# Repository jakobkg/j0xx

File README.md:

# j0xx
A controller inspired by the Frame1 and Smashbox controllers

## Case
### BOM
 - 36 M2 screws, countersunk head recommended
   - 28x 10mm
   - 8x 5mm
 - 18 M2 threaded spacers
   - 18x 10mm
 - 35 pieces of wire, stranded or solid core

## PCBs
The PCB files in this repository are all made using KiCad 6, and may not work properly in earlier versions. Most files are only plain PCBs, but the "main board" files also hold part numbers and information needed to place an order including assembly through JLCPCB.

## Build notes
***Due to height constraints, surface mounted LEDs can not be used along with low profile Choc switches in this iteration of the design***

The controller case is designed to be made out of cut sheets of material, such as laser cut wood/acrylic or metal.
I recommend a thickness of 3mm for the top plate for use with low profile Choc switches, and 6mm for use with regular MX switches to ensure keycaps protrude nicely without the sides of the switches being exposed.
The switch mounting plate needs to be 1.5mm thick to fit the Cherry MX/Kailh Choc design specs and ensure a good fit, thinner plates may cause poor mounting and thicker plates will interfere with Choc switch mounting.

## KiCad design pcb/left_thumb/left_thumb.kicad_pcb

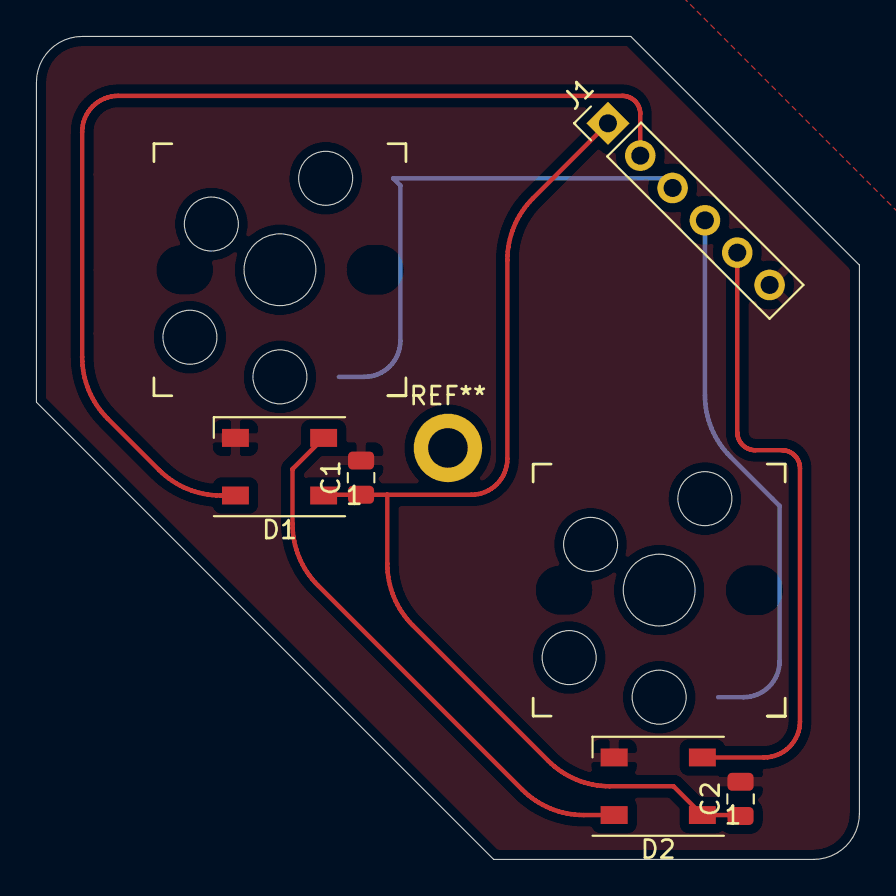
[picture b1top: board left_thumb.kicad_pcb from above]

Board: 2 copper layers, 45.7 x 45.7 mm, 7 parts (0 on the bottom side), 7 nets.

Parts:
C1, C2: C; C_0805_2012Metric
D1, D2: WS2812B; LED_WS2812B_PLCC4_5.0x5.0mm_P3.2mm
J1: Conn_01x06; PinHeader_1x06_P2.54mm_Vertical
SW1, SW2: SW_Push; MX+Choc_socket

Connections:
+5V: C1.1, C2.1, D1.1, D2.1, J1.1
BTN_MODX: J1.3, SW1.1
BTN_MODY: J1.4, SW2.1
GND: C1.2, C2.2, D1.3, D2.3, J1.6, SW1.2, SW2.2
LED_IN: D1.4, J1.2
LED_OUT: D2.2, J1.5
unnamed: D1.2, D2.4

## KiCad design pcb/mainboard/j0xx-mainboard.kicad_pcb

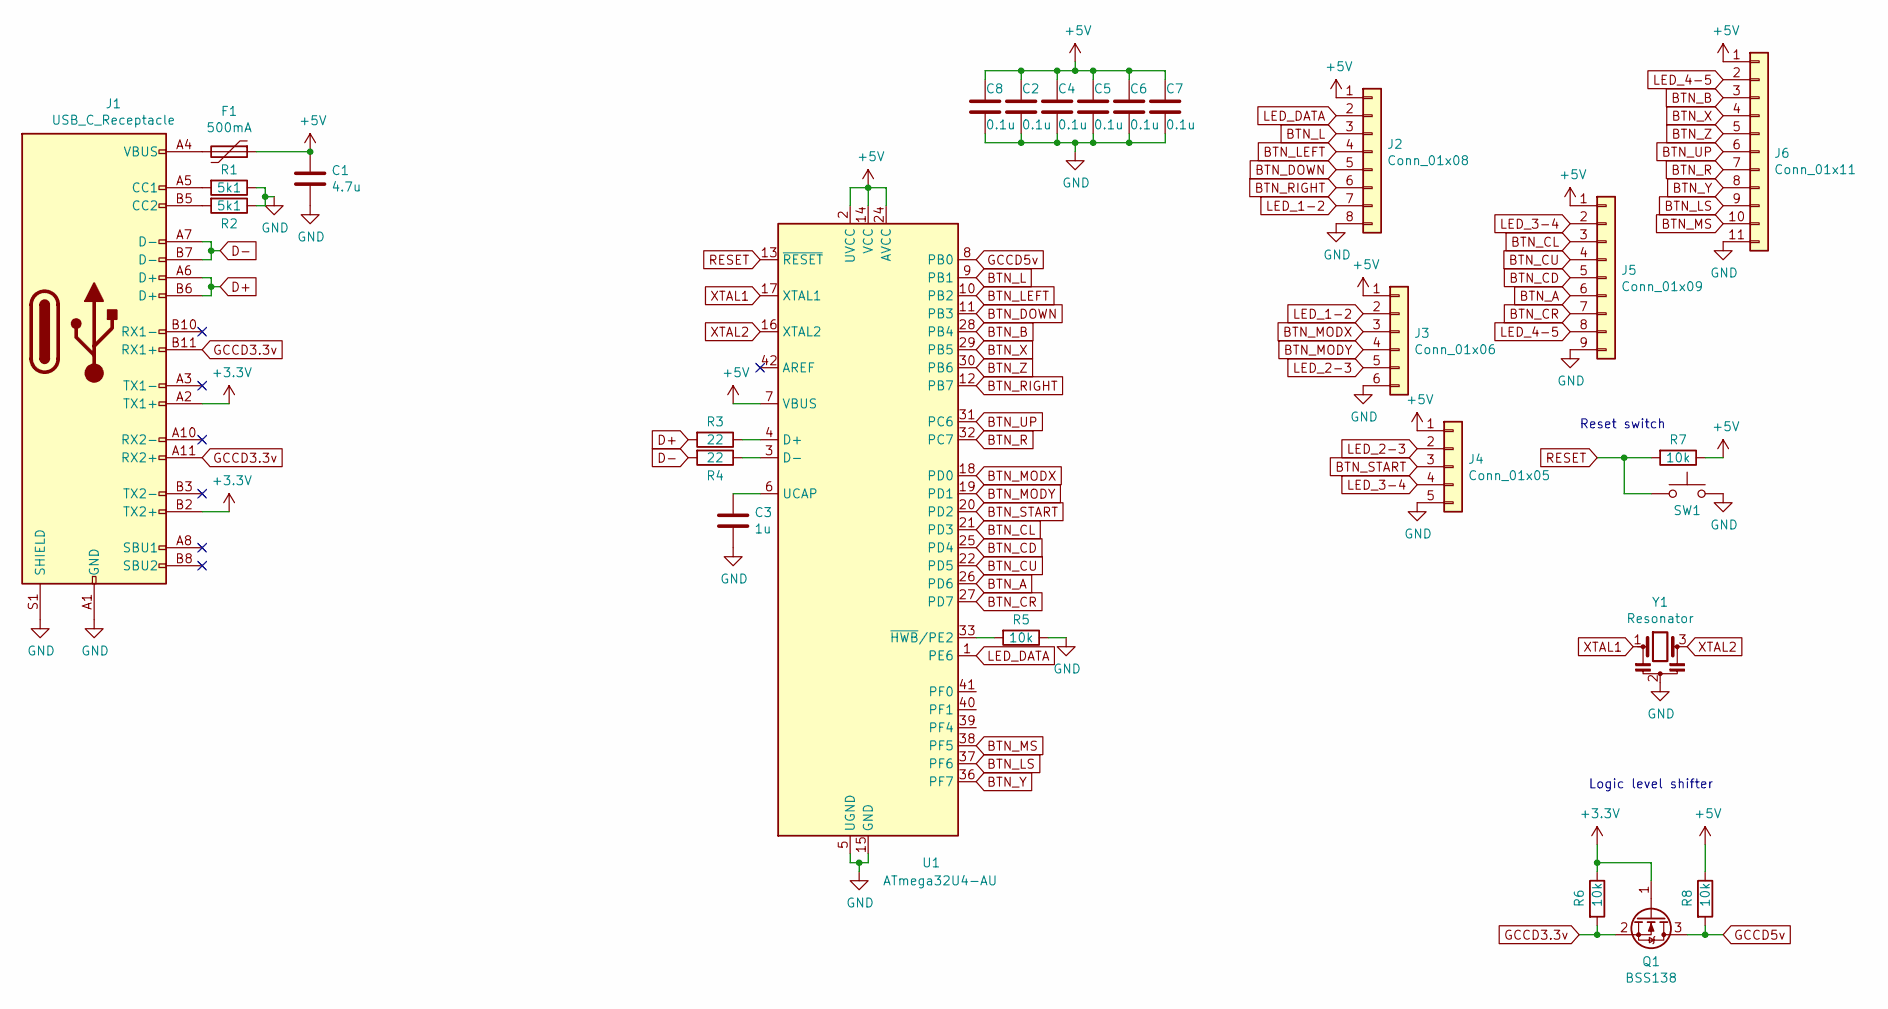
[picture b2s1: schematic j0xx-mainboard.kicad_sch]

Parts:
C1: 4.7u; C_0805_2012Metric; LCSC C1779
C2, C4, C5, C6, C7, C8: 0.1u; C_0805_2012Metric; LCSC C28233
C3: 1u; C_0805_2012Metric; LCSC C28323
F1: 500mA; Fuse_1206_3216Metric; LCSC C261952
J1: USB_C_Receptacle; USB_C_LCSC_C456013; LCSC C456013
J2: Conn_01x08; PinHeader_1x08_P2.54mm_Vertical
J3: Conn_01x06; PinHeader_1x06_P2.54mm_Vertical
J4: Conn_01x05; PinHeader_1x05_P2.54mm_Vertical
J5: Conn_01x09; PinHeader_1x09_P2.54mm_Vertical
J6: Conn_01x11; PinHeader_1x11_P2.54mm_Vertical
Q1: BSS138; SOT-23; LCSC C427380
R1, R2: 5k1; R_0805_2012Metric; LCSC C27834
R3, R4: 22; R_0805_2012Metric; LCSC C17561
R5, R6, R7, R8: 10k; R_0805_2012Metric; LCSC C17414
SW1: reset; TestPoint_2Pads_Pitch2.54mm_Drill0.8mm
U1: ATmega32U4-AU; TQFP-44_10x10mm_P0.8mm; LCSC C112161
Y1: Resonator; Resonator_SMD_Murata_CSTxExxV-3Pin_3.0x1.1mm; LCSC C341521

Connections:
+3V3: J1.A2 (TX1+), J1.B2 (TX2+), Q1.1 (G), R6.1
+5V: C1.1, C2.1, C4.1, C5.1, C6.1, C7.1, C8.1, F1.1, J2.1, J3.1, J4.1, J5.1, J6.1, R7.1, R8.1, U1.2 (UVCC), U1.7 (VBUS), U1.14 (VCC), U1.24 (AVCC), U1.34 (VCC), U1.44 (AVCC)
BTN_A: J5.6, U1.26 (PD6)
BTN_B: J6.3, U1.28 (PB4)
BTN_CD: J5.5, U1.25 (PD4)
BTN_CL: J5.3, U1.21 (PD3)
BTN_CR: J5.7, U1.27 (PD7)
BTN_CU: J5.4, U1.22 (PD5)
BTN_DOWN: J2.5, U1.11 (PB3)
BTN_L: J2.3, U1.9 (PB1)
BTN_LEFT: J2.4, U1.10 (PB2)
BTN_LS: J6.9, U1.37 (PF6)
BTN_MODX: J3.3, U1.18 (PD0)
BTN_MODY: J3.4, U1.19 (PD1)
BTN_MS: J6.10, U1.38 (PF5)
BTN_R: J6.7, U1.32 (PC7)
BTN_RIGHT: J2.6, U1.12 (PB7)
BTN_START: J4.3, U1.20 (PD2)
BTN_UP: J6.6, U1.31 (PC6)
BTN_X: J6.4, U1.29 (PB5)
BTN_Y: J6.8, U1.36 (PF7)
BTN_Z: J6.5, U1.30 (PB6)
D+: J1.A6 (D+), J1.B6 (D+), R3.2
D-: J1.A7 (D-), J1.B7 (D-), R4.2
GCCD3.3v: J1.A11 (RX2+), J1.B11 (RX1+), Q1.2 (S), R6.2
GCCD5v: Q1.3 (D), R8.2, U1.8 (PB0)
GND: C1.2, C2.2, C3.2, C4.2, C5.2, C6.2, C7.2, C8.2, J1.A1 (GND), J1.A12 (GND), J1.B1 (GND), J1.B12 (GND), J1.S1 (SHIELD), J2.8, J3.6, J4.5, J5.9, J6.11, R1.1, R2.1, R5.1, SW1.2, U1.5 (UGND), U1.15 (GND), U1.23 (GND), U1.35 (GND), U1.43 (GND), Y1.2
LED_1-2: J2.7, J3.2
LED_2-3: J3.5, J4.2
LED_3-4: J4.4, J5.2
LED_4-5: J5.8, J6.2
LED_DATA: J2.2, U1.1 (PE6)
unnamed: C3.1, U1.6 (UCAP)
unnamed: F1.2, J1.A4 (VBUS), J1.A9 (VBUS), J1.B4 (VBUS), J1.B9 (VBUS)
unnamed: J1.A5 (CC1), R1.2
unnamed: J1.B5 (CC2), R2.2
unnamed: R3.1, U1.4 (D+)
unnamed: R4.1, U1.3 (D-)
unnamed: R5.2, U1.33 (~HWB/PE2)
RESET: R7.2, SW1.1, U1.13 (~RESET)
XTAL1: U1.17 (XTAL1), Y1.1
XTAL2: U1.16 (XTAL2), Y1.3

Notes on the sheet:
Logic level shifter
Reset switch

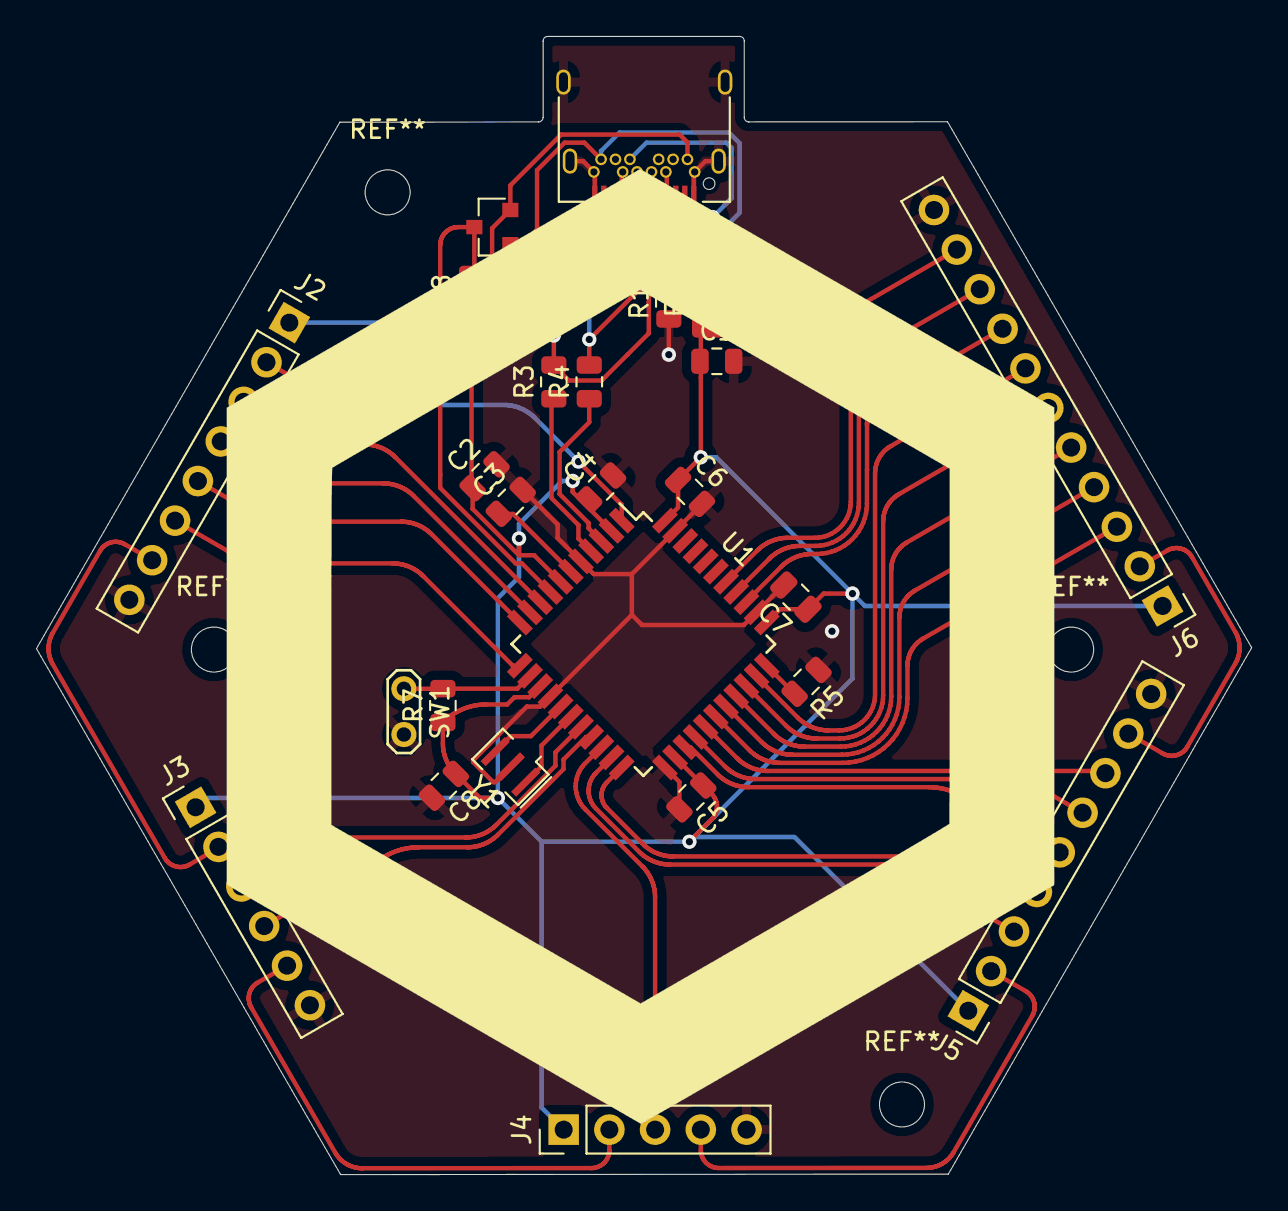
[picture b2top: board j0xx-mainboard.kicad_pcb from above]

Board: 2 copper layers, 67.5 x 63.2 mm, 27 parts (0 on the bottom side), 42 nets.

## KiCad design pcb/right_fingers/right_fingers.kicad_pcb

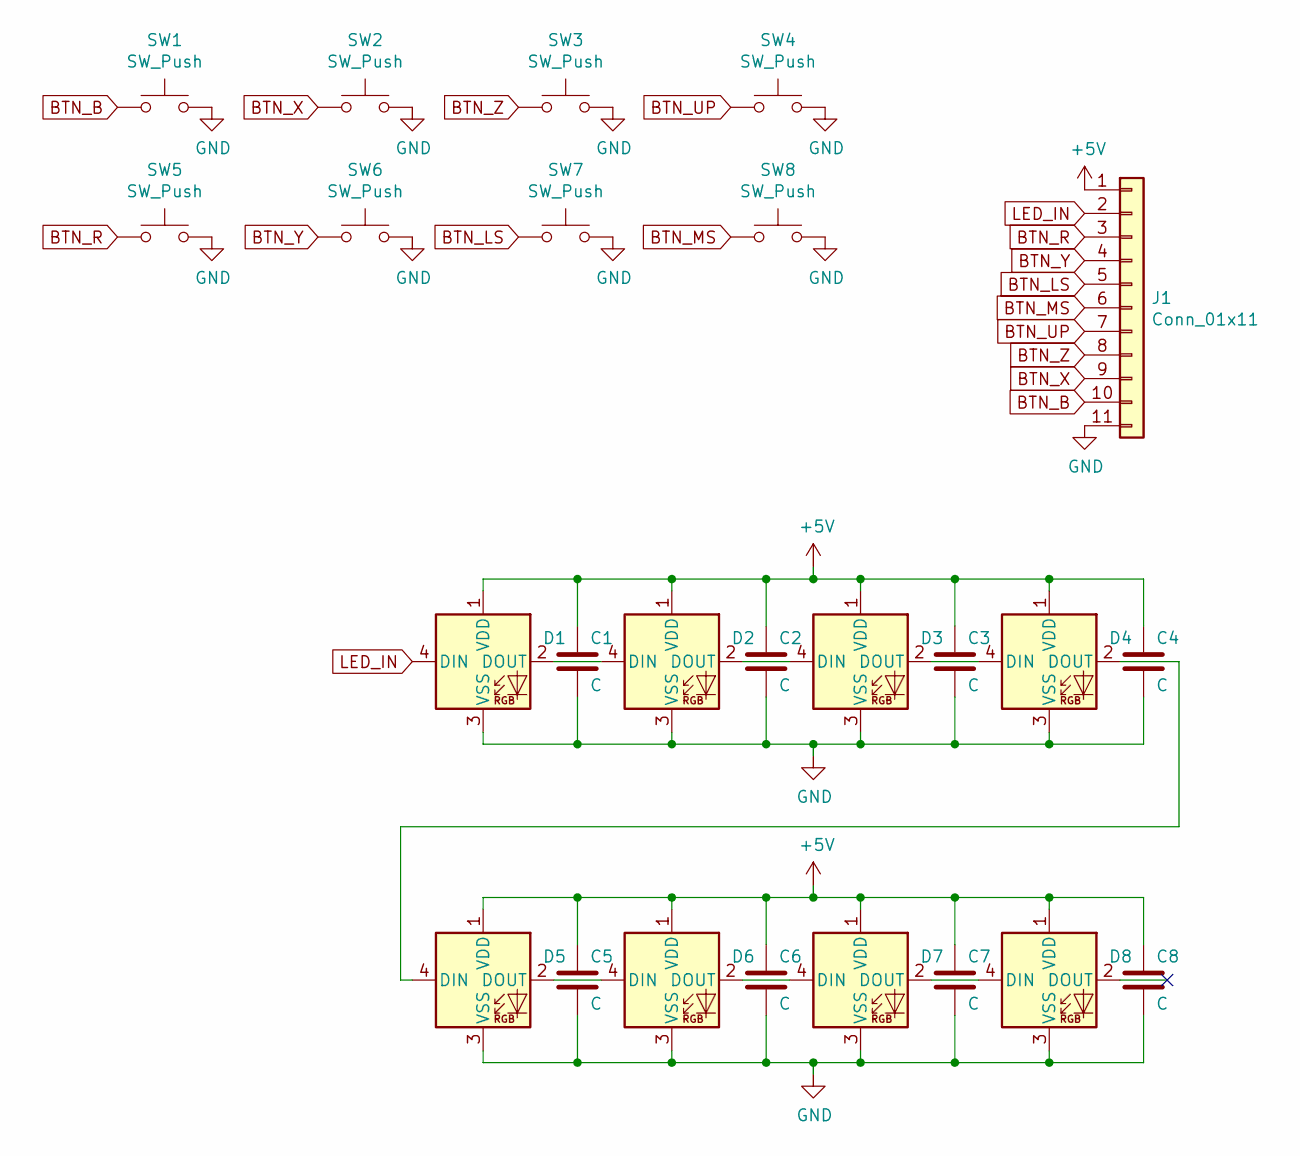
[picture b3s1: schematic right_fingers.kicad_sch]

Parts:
C1, C2, C3, C4, C5, C6, C7, C8: C; C_0805_2012Metric
D1, D2, D3, D4, D5, D6, D7, D8: WS2812B; LED_WS2812B_PLCC4_5.0x5.0mm_P3.2mm
J1: Conn_01x11; PinHeader_1x11_P2.54mm_Vertical
SW1, SW2, SW3, SW4, SW5, SW6, SW7, SW8: SW_Push; MX+Choc_socket

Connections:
+5V: C1.1, C2.1, C3.1, C4.1, C5.1, C6.1, C7.1, C8.1, D1.1 (VDD), D2.1 (VDD), D3.1 (VDD), D4.1 (VDD), D5.1 (VDD), D6.1 (VDD), D7.1 (VDD), D8.1 (VDD), J1.1
BTN_B: J1.10, SW1.1
BTN_LS: J1.5, SW7.1
BTN_MS: J1.6, SW8.1
BTN_R: J1.3, SW5.1
BTN_UP: J1.7, SW4.1
BTN_X: J1.9, SW2.1
BTN_Y: J1.4, SW6.1
BTN_Z: J1.8, SW3.1
GND: C1.2, C2.2, C3.2, C4.2, C5.2, C6.2, C7.2, C8.2, D1.3 (VSS), D2.3 (VSS), D3.3 (VSS), D4.3 (VSS), D5.3 (VSS), D6.3 (VSS), D7.3 (VSS), D8.3 (VSS), J1.11, SW1.2, SW2.2, SW3.2, SW4.2, SW5.2, SW6.2, SW7.2, SW8.2
LED_IN: D1.4 (DIN), J1.2
unnamed: D1.2 (DOUT), D2.4 (DIN)
unnamed: D2.2 (DOUT), D3.4 (DIN)
unnamed: D3.2 (DOUT), D4.4 (DIN)
unnamed: D4.2 (DOUT), D5.4 (DIN)
unnamed: D5.2 (DOUT), D6.4 (DIN)
unnamed: D6.2 (DOUT), D7.4 (DIN)
unnamed: D7.2 (DOUT), D8.4 (DIN)

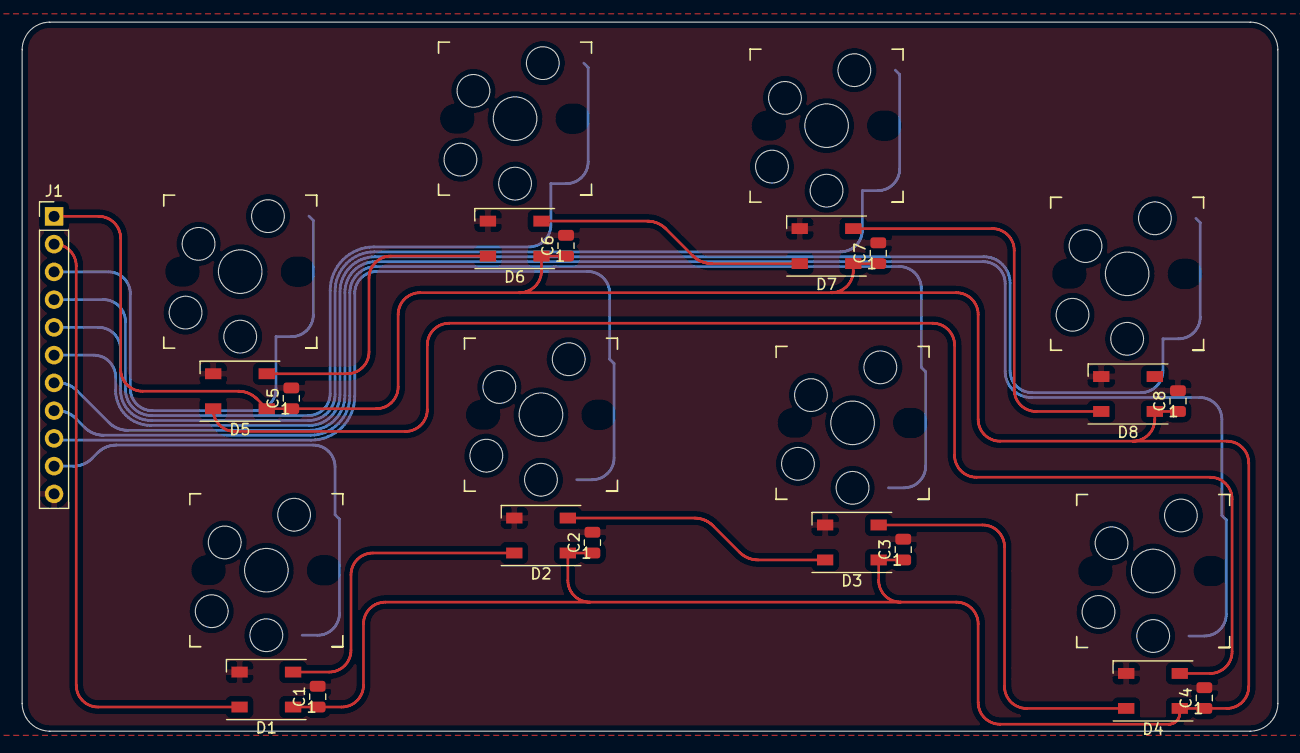
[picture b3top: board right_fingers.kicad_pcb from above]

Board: 2 copper layers, 114.9 x 64.9 mm, 25 parts (0 on the bottom side), 18 nets.

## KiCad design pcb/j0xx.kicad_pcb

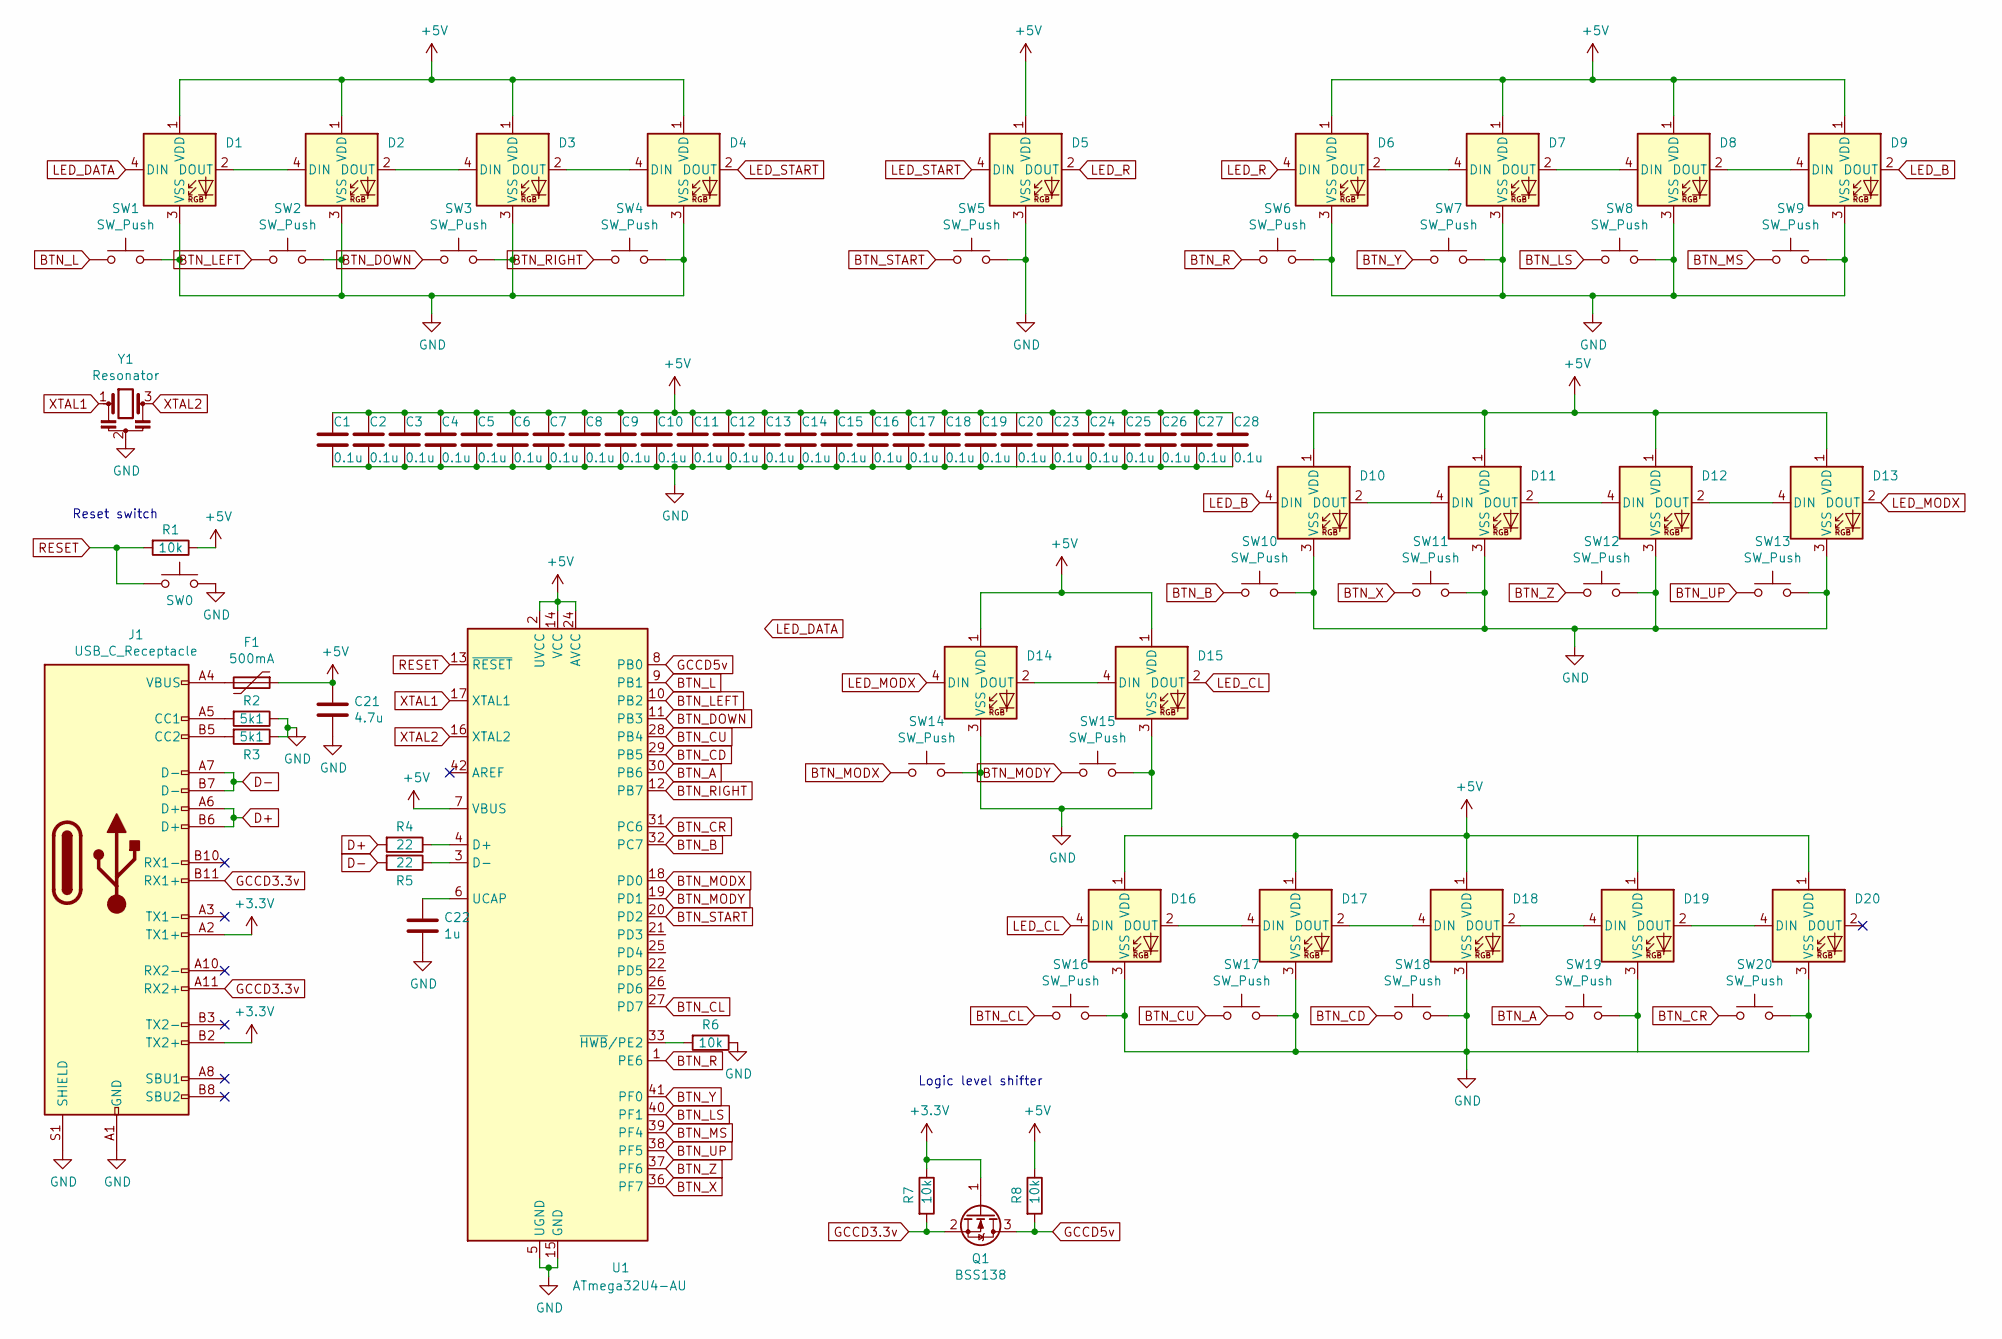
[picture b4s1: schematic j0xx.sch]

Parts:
C1, C2, C3, C4, C5, C6, C7, C8, C9, C10, C11, C12, C13, C14, C15, C16, C17, C18, C19, C20, C23, C24, C25, C26, C27, C28: 0.1u; C_0805_2012Metric
C21: 4.7u; C_0805_2012Metric
C22: 1u; C_0805_2012Metric
D1, D2, D3, D4, D5, D6, D7, D8, D9, D10, D11, D12, D13, D14, D15, D16, D17, D18, D19, D20: WS2812B; LED_WS2812B_PLCC4_5.0x5.0mm_P3.2mm
F1: 500mA; Fuse_1206_3216Metric
J1: USB_C_Receptacle; USB_C_Receptacle_Amphenol_12401610E4-2A
Q1: BSS138; SOT-23
R1, R6, R7, R8: 10k; R_0805_2012Metric
R2, R3: 5k1; R_0805_2012Metric
R4, R5: 22; R_0805_2012Metric
SW0: reset; TestPoint_2Pads_Pitch2.54mm_Drill0.8mm
SW1, SW2, SW3, SW4, SW5, SW6, SW7, SW8, SW9, SW10, SW11, SW12, SW13, SW14, SW15, SW16, SW17, SW18, SW19, SW20: SW_Push; MX+Choc_socket
U1: ATmega32U4-AU; TQFP-44_10x10mm_P0.8mm
Y1: Resonator; Resonator_SMD_muRata_CSTxExxV-3Pin_3.0x1.1mm

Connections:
+3V3: J1.A2 (TX1+), J1.B2 (TX2+), Q1.1 (G), R7.1
+5V: C1.1, C2.1, C3.1, C4.1, C5.1, C6.1, C7.1, C8.1, C9.1, C10.1, C11.1, C12.1, C13.1, C14.1, C15.1, C16.1, C17.1, C18.1, C19.1, C20.1, C21.1, C23.1, C24.1, C25.1, C26.1, C27.1, C28.1, D1.1 (VDD), D2.1 (VDD), D3.1 (VDD), D4.1 (VDD), D5.1 (VDD), D6.1 (VDD), D7.1 (VDD), D8.1 (VDD), D9.1 (VDD), D10.1 (VDD), D11.1 (VDD), D12.1 (VDD), D13.1 (VDD), D14.1 (VDD), D15.1 (VDD), D16.1 (VDD), D17.1 (VDD), D18.1 (VDD), D19.1 (VDD), D20.1 (VDD), F1.1, R1.1, R8.1, U1.2 (UVCC), U1.7 (VBUS), U1.14 (VCC), U1.24 (AVCC), U1.34 (VCC), U1.44 (AVCC)
BTN_A: SW19.1, U1.30 (PB6)
BTN_B: SW10.1, U1.32 (PC7)
BTN_CD: SW18.1, U1.29 (PB5)
BTN_CL: SW16.1, U1.27 (PD7)
BTN_CR: SW20.1, U1.31 (PC6)
BTN_CU: SW17.1, U1.28 (PB4)
BTN_DOWN: SW3.1, U1.11 (PB3)
BTN_L: SW1.1, U1.9 (PB1)
BTN_LEFT: SW2.1, U1.10 (PB2)
BTN_LS: SW8.1, U1.40 (PF1)
BTN_MODX: SW14.1, U1.18 (PD0)
BTN_MODY: SW15.1, U1.19 (PD1)
BTN_MS: SW9.1, U1.39 (PF4)
BTN_R: SW6.1, U1.1 (PE6)
BTN_RIGHT: SW4.1, U1.12 (PB7)
BTN_START: SW5.1, U1.20 (PD2)
BTN_UP: SW13.1, U1.38 (PF5)
BTN_X: SW11.1, U1.36 (PF7)
BTN_Y: SW7.1, U1.41 (PF0)
BTN_Z: SW12.1, U1.37 (PF6)
D+: J1.A6 (D+), J1.B6 (D+), R4.2
D-: J1.A7 (D-), J1.B7 (D-), R5.2
GCCD3.3v: J1.A11 (RX2+), J1.B11 (RX1+), Q1.2 (S), R7.2
GCCD5v: Q1.3 (D), R8.2, U1.8 (PB0)
GND: C1.2, C2.2, C3.2, C4.2, C5.2, C6.2, C7.2, C8.2, C9.2, C10.2, C11.2, C12.2, C13.2, C14.2, C15.2, C16.2, C17.2, C18.2, C19.2, C20.2, C21.2, C22.2, C23.2, C24.2, C25.2, C26.2, C27.2, C28.2, D1.3 (VSS), D2.3 (VSS), D3.3 (VSS), D4.3 (VSS), D5.3 (VSS), D6.3 (VSS), D7.3 (VSS), D8.3 (VSS), D9.3 (VSS), D10.3 (VSS), D11.3 (VSS), D12.3 (VSS), D13.3 (VSS), D14.3 (VSS), D15.3 (VSS), D16.3 (VSS), D17.3 (VSS), D18.3 (VSS), D19.3 (VSS), D20.3 (VSS), J1.A1 (GND), J1.A12 (GND), J1.B1 (GND), J1.B12 (GND), J1.S1 (SHIELD), R2.1, R3.1, R6.1, SW0.2, SW1.2, SW2.2, SW3.2, SW4.2, SW5.2, SW6.2, SW7.2, SW8.2, SW9.2, SW10.2, SW11.2, SW12.2, SW13.2, SW14.2, SW15.2, SW16.2, SW17.2, SW18.2, SW19.2, SW20.2, U1.5 (UGND), U1.15 (GND), U1.23 (GND), U1.35 (GND), U1.43 (GND), Y1.2
LED_B: D9.2 (DOUT), D10.4 (DIN)
LED_CL: D15.2 (DOUT), D16.4 (DIN)
LED_MODX: D13.2 (DOUT), D14.4 (DIN)
LED_R: D5.2 (DOUT), D6.4 (DIN)
LED_START: D4.2 (DOUT), D5.4 (DIN)
unnamed: C22.1, U1.6 (UCAP)
unnamed: D1.2 (DOUT), D2.4 (DIN)
unnamed: D2.2 (DOUT), D3.4 (DIN)
unnamed: D3.2 (DOUT), D4.4 (DIN)
unnamed: D6.2 (DOUT), D7.4 (DIN)
unnamed: D7.2 (DOUT), D8.4 (DIN)
unnamed: D8.2 (DOUT), D9.4 (DIN)
unnamed: D10.2 (DOUT), D11.4 (DIN)
unnamed: D11.2 (DOUT), D12.4 (DIN)
unnamed: D12.2 (DOUT), D13.4 (DIN)
unnamed: D14.2 (DOUT), D15.4 (DIN)
unnamed: D16.2 (DOUT), D17.4 (DIN)
unnamed: D17.2 (DOUT), D18.4 (DIN)
unnamed: D18.2 (DOUT), D19.4 (DIN)
unnamed: D19.2 (DOUT), D20.4 (DIN)
unnamed: F1.2, J1.A4 (VBUS), J1.A9 (VBUS), J1.B4 (VBUS), J1.B9 (VBUS)
unnamed: J1.A5 (CC1), R2.2
unnamed: J1.B5 (CC2), R3.2
unnamed: R4.1, U1.4 (D+)
unnamed: R5.1, U1.3 (D-)
unnamed: R6.2, U1.33 (~HWB~/PE2)
RESET: R1.2, SW0.1, U1.13 (~RESET)
XTAL1: U1.17 (XTAL1), Y1.1
XTAL2: U1.16 (XTAL2), Y1.3

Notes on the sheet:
Logic level shifter
Reset switch

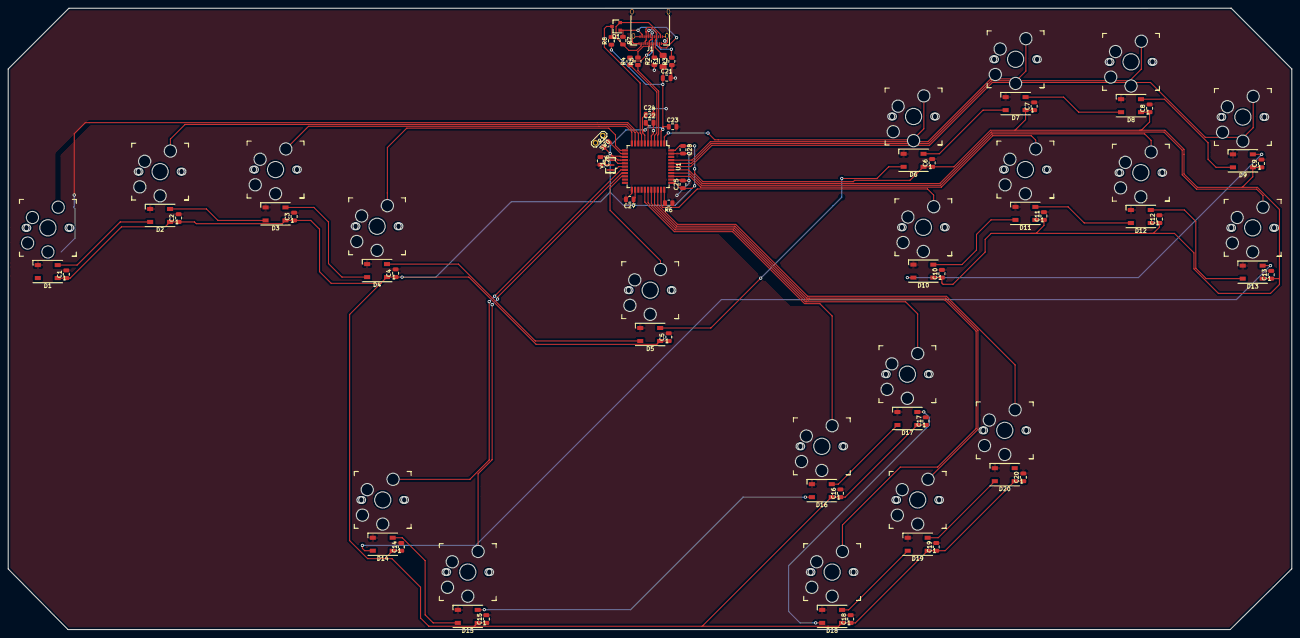
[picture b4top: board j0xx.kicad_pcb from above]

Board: 2 copper layers, 316.3 x 153.1 mm, 82 parts (0 on the bottom side), 56 nets.

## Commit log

2021-08-04 move pcb files a dir up
2021-08-04 added footprints
2021-08-05 Initial PCB work
2021-08-07 More PCB work, rearrange some MCU pins
2021-08-08 First PCB draft complete
2021-08-09 Add dual hotswap footprint
2021-08-10 Start splitting PCB into modules
2021-08-20 rearrange parts, add connectors and outline
2021-08-22 Protruding USB port, tilted MCU
2021-09-15 Add most PCB modules
2021-09-16 Finish button cluster PCB drafts
2022-01-12 First full iteration of physical design
2022-01-12 Remove unneeded git files
2022-02-08 add MX switch plate, fix mis-sized screw hole
